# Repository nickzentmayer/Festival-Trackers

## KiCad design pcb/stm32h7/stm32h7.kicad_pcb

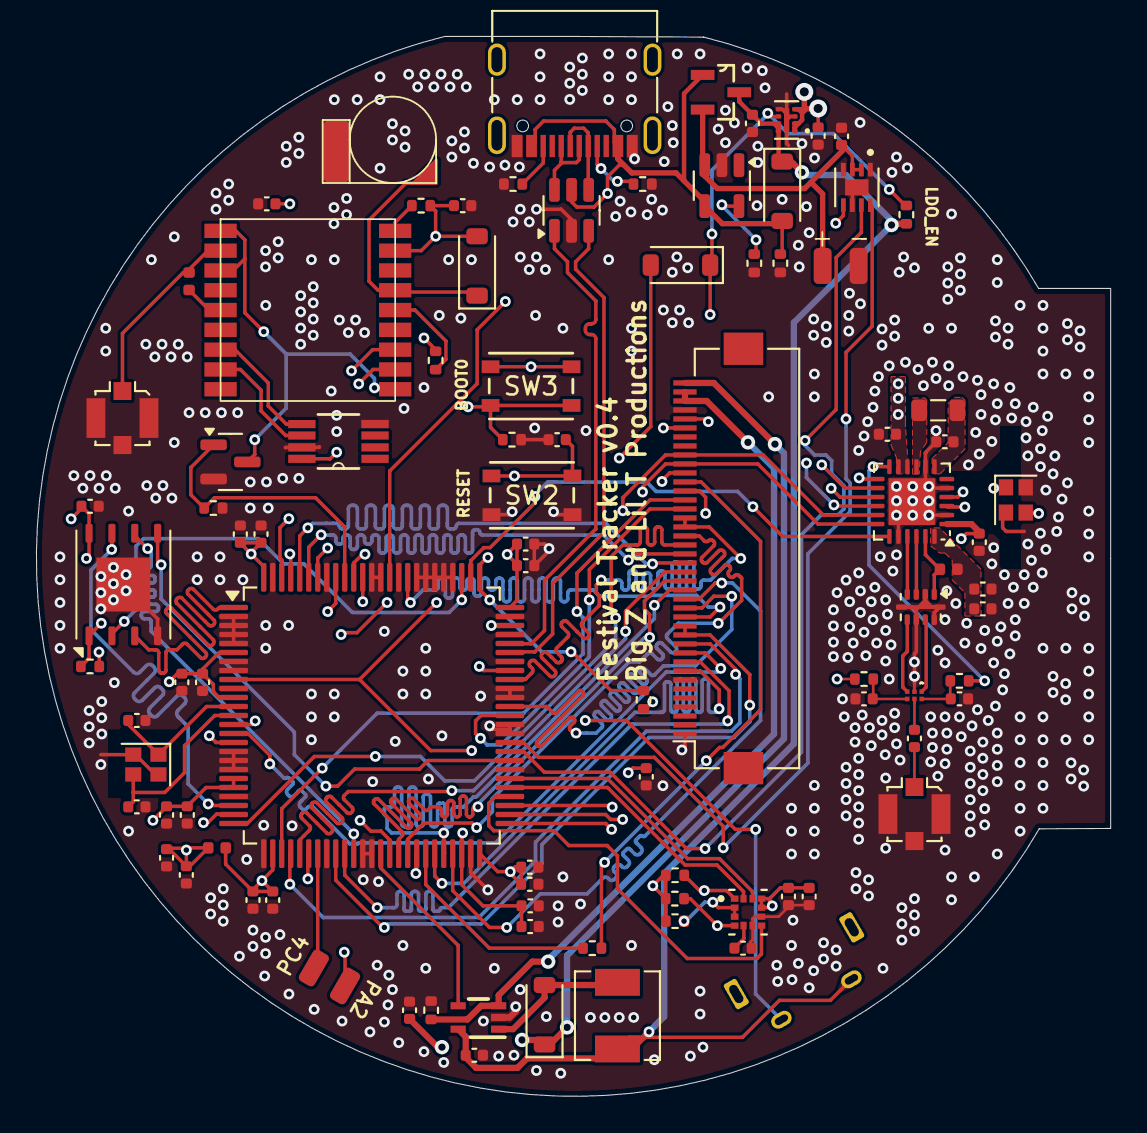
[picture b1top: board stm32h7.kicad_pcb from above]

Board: 6 copper layers, 59.7 x 58.9 mm, 93 parts (0 on the bottom side), 95 nets.

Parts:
ATGM336H1: ATGM336H
BT1: MS421R; MSR421R
C1, C2: 200nF; C_0402_1005Metric
C3, C7, C9, C12, C17, C22: 1uF; C_0402_1005Metric
C4, C5: 8pF; C_0402_1005Metric
C6, C8, C10, C11, C13, C16, C18, C24, C25, C26, C27, C28, C29, C30, C34, C35, C36, C37, C38: 100nF; C_0402_1005Metric
C14: 4.7uF; C_0402_1005Metric
C15, C39: 10uF; C_0402_1005Metric
C19: 39pF; C_0402_1005Metric
C20: 47nF; C_0402_1005Metric
C21: 470nF; C_0402_1005Metric
C23: 47pF; C_0402_1005Metric
C31, C32: 1nF; C_0402_1005Metric
C33: 220nF; C_0402_1005Metric
D1, D2, D3, D4: MBR0540; D_SOD-123
FB1: FerriteBead; L_0402_1005Metric
FL1: 0900FM15K0039; Balun_Johanson_0900FM15K0039
J1: USB_C_Receptacle_USB2.0_14P; USB_C_Receptacle_G-Switch_GT-USB-7010ASV
J2: Battery; 2 Wire Pads
J3: GPS_ANT; U.FL_Molex_MCRF_73412-0110_Vertical
J4: Conn_Coaxial; U.FL_Molex_MCRF_73412-0110_Vertical
J5: Conn_01x40_Socket; Hirose_FH12-40S-0.5SH_1x40-1MP_P0.50mm_Horizontal
J6: Test Pads; 2 Wire Pads
L1: 4.7uH; L_Sunlord_MWSA0402S
L3, L5: 47nH; L_0402_1005Metric
L4: 15uH; L_0805_2012Metric
Q1: DMG3414U; SOT-23
Q1_Xtal1: 32.0MHz; Crystal_SMD_2016-4Pin_2.0x1.6mm
R1, R4, R10, R18: 10k; R_0402_1005Metric
R2: 10R; R_0402_1005Metric
R3: 200k; R_0402_1005Metric
R5, R12, R13: 100R; R_0402_1005Metric
R6, R7, R8: 5.1k; R_0402_1005Metric
R9: 100k; R_0402_1005Metric
R11: 0R; R_0402_1005Metric
R15, R16, R17, R19: 10K; R_0402_1005Metric
SW1: SW_Push; vert_button_6mm
SW2, SW3: SW_Push; SW4_PTS815 SJM 250 SMTR LFS_CNK
U1: STM32H743VGTx; LQFP-100_14x14mm_P0.5mm
U2: NCP186AMX330TAG; PSON40P160X120X45-9N
U3: USBLC6-2SC6; SOT-23-6
U4: MCP73831-2-OT; SOT-23-5
U5: 24AA32AF-I_MS; SOP65P490X110-8N
U6: SX1262IMLTRT; QFN-24-1EP_4x4mm_P0.5mm_EP2.6x2.6mm
U7: DMG3415U-7; SOT95P240X105-3N
U8: LSM303AGR; PQFN50P200X200X100-12N
U9: MT25QUxxxxxx1xW7; W-PDFN-8-1EP_6x5mm_P1.27mm_EP3x3mm
U10: MAX17048G_T10; SON50P200X200X80-9N
U11: TPS61169DCKR; DCK0005A_N
U12: BGS12SN6E6327XTSA1; TSNP-6-2&slash_-8_INF
Y1: 25MHz; Crystal_SMD_2016-4Pin_2.0x1.6mm

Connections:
+3V3: ATGM336H1.8 (VCC), C7.1, C8.1, C9.1, C10.1, C11.1, C12.2, C15.1, C16.1, C17.1, C18.1, C24.1, C25.1, C26.1, C27.1, C28.1, C29.1, C30.1, C34.1, C35.1, C36.1, C37.1, C38.2, C39.2, D2.2 (A), FB1.1, FB1.2, J5.36, R3.1, R4.1, R13.2, R15.1, R16.1, R17.1, R18.2, R19.2, SW3.1, SW3.2, U1.6 (VBAT), U1.11 (VDD), U1.20 (VREF+), U1.21 (VDDA), U1.27 (VDD), U1.50 (VDD), U1.75 (VDD), U1.100 (VDD), U2.1 (OUT), U2.2 (OUT__1), U2.4 (FB/ADJ), U5.8 (VCC), U6.1 (VDD_IN), U6.10 (VBAT), U6.11 (VBAT_IO), U8.9 (VDD), U8.10 (VDD_IO), U9.8 (VCC)
+BATT: C13.1, J2.1, U4.3 (V_{BAT}), U7.2 (S), U10.2 (CELL), U10.3 (VDD)
/Accel & Magnetometer/CS_MAG: R15.2, U8.2 (CS_XL), U8.3 (CS_MAG)
/gps/ON/OFF: ATGM336H1.5 (ON/OFF), R4.2
ANT_SW_CTRL: R12.2, U6.12 (DIO2)
BL_ANODE: C22.2, D3.1 (K), J5.40
BL_CATHODE: J5.38, J5.39, R2.2, U11.3 (FB)
BTN: D4.2 (A), SW1.1, U1.9 (PC15)
FG_NALERT: U1.86 (PD5), U10.5 (~ALERT)
GND: BT1.2 (-), C1.1, C2.1, C3.1, C4.2, C5.1, C6.1, C7.2, C8.2, C9.2, C10.2, C11.2, C12.1, C13.2, C14.2, C15.2, C16.2, C17.2, C18.2, C20.2, C21.2, C22.1, C23.2, C24.2, C25.2, C26.2, C27.2, C28.2, C29.2, C30.2, C31.2, C32.2, C33.2, C34.2, C35.2, C36.2, C37.2, C38.1, C39.1, FL1.2 (GND), FL1.5 (GND), FL1.7 (GND), FL1.9 (GND), FL1.10 (GND), J1.A1 (GND), J1.A12 (GND), J1.B1 (GND), J1.B12 (GND), J2.2, J3.2 (Ext), J4.2 (Ext), J5.1, J5.7, J5.37, Q1.2 (S), Q1_Xtal1.2, Q1_Xtal1.4, R1.2, R2.1, R6.2, R7.2, R8.2, R9.2, R10.1, SW2.3, SW2.4, U1.2 (PE3), U1.3 (PE4), U1.4 (PE5), U1.5 (PE6), U1.7 (PC13), U1.8 (PC14), U1.10 (VSS), U1.17 (PC2_C), U1.18 (PC3_C), U1.19 (VSSA), U1.22 (PA0), U1.26 (VSS), U1.33 (PC5), U1.37 (PE7), U1.38 (PE8), U1.49 (VSS), U1.57 (PD10), U1.61 (PD14), U1.62 (PD15), U1.65 (PC8), U1.66 (PC9), U1.69 (PA10), U1.72 (PA13), U1.74 (VSS), U1.79 (PC11), U1.80 (PC12), U1.81 (PD0), U1.82 (PD1), U1.83 (PD2), U1.85 (PD4), U1.87 (PD6), U1.88 (PD7), U1.93 (PB7), U1.99 (VSS), U2.3 (N/C), U2.5 (GND), U2.9 (EPAD), U3.2 (GND), U4.2 (V_{SS}), U5.4 (VSS), U5.7 (WP), U6.2 (GND), U6.5 (GND), U6.8 (GND), U6.20 (GND), U6.25 (GND), U8.6 (GND), U8.8 (GND), U9.4 (VSS), U9.9 (PAD), U10.1 (CTG), U10.4 (GND), U10.6 (QSTRT), U10.9 (EP), U11.2 (GND), U12.2 (GND), Y1.2, Y1.4
GPS_ON: Q1.1 (G), R10.2, U1.91 (PB5)
GPS_RESET: ATGM336H1.9 (nReset), R3.2
GPS_RXD: ATGM336H1.3 (RXD), U1.98 (PE1)
GPS_TXD: ATGM336H1.2 (TXD), U1.97 (PE0)
INT_MAG: U1.54 (PB15), U8.7 (INT_MAG/DRDY)
LCD_B1: J5.24, J5.25, U1.67 (PA8)
LCD_B2: J5.23, U1.42 (PE12)
LCD_B3: J5.22, U1.25 (PA3)
LCD_B4: J5.21, U1.95 (PB8)
LCD_B5: J5.20, U1.96 (PB9)
LCD_BL: U1.39 (PE9), U11.4 (CTRL)
LCD_CS: J5.30, R19.1, U1.76 (PA14)
LCD_DE: J5.28, U1.43 (PE13)
LCD_G0: J5.19, U1.30 (PA6)
LCD_G1: J5.18, U1.41 (PE11)
LCD_G2: J5.17, U1.46 (PB10)
LCD_G3: J5.16, U1.47 (PB11)
LCD_G4: J5.15, U1.64 (PC7)
LCD_G5: J5.14, U1.84 (PD3)
LCD_HSYNC: J5.26, U1.63 (PC6)
LCD_PCLK: R5.1, U1.44 (PE14)
LCD_R1: J5.12, J5.13, U1.34 (PB0)
LCD_R2: J5.11, U1.29 (PA5)
LCD_R3: J5.10, U1.15 (PC0)
LCD_R4: J5.9, U1.35 (PB1)
LCD_R5: J5.8, U1.45 (PE15)
LCD_RST: J5.35, U1.40 (PE10)
LCD_VSYNC: J5.27, U1.28 (PA4)
LDO_EN: D4.1 (K), R11.1, U1.16 (PC1), U2.6 (EN)
LoRa_BUSY: U1.53 (PB14), U6.14 (BUSY)
LoRa_DIO1: U1.52 (PB13), U6.13 (DIO1)
LoRa_NSS: U1.77 (PA15), U6.19 (NSS)
LoRa_RST: U1.51 (PB12), U6.15 (~RESET)
MISO: U1.90 (PB4), U6.16 (MISO)
MOSI: J5.32, U1.31 (PA7), U6.17 (MOSI)
NRST: C6.2, SW2.1, SW2.2, U1.14 (NRST)
unnamed: ATGM336H1.1 (GND), Q1.3 (D)
unnamed: ATGM336H1.11 (RF_IN), J3.1 (In), L3.1
unnamed: ATGM336H1.17 (SCL), U5.6 (SCL)
unnamed: ATGM336H1.16 (SDA), U5.5 (SDA)
unnamed: ATGM336H1.6 (VBAT), BT1.1 (+), D2.1 (K)
unnamed: ATGM336H1.14 (VCC_RF), L3.2
unnamed: C1.2, C2.2, U1.48 (VCAP), U1.73 (VCAP)
unnamed: D3.2 (A), L1.2, U11.1 (SW)
unnamed: FL1.3 (RFI_N), U6.22 (RFI_N)
unnamed: FL1.4 (RFI_P), U6.21 (RFI_P)
unnamed: FL1.1 (RFO), L5.2, U6.23 (RFO)
unnamed: FL1.6 (SW_RFI), U12.3 (RF1)
unnamed: FL1.8 (SW_RFO), U12.1 (RF2)
unnamed: J1.A5 (CC1), R7.1
unnamed: J1.B5 (CC2), R6.1
unnamed: J1.A6 (D+), J1.B6 (D+), U3.6 (I/O1)
unnamed: J1.A7 (D-), J1.B7 (D-), U3.4 (I/O2)
unnamed: C19.1, J4.1 (In)
unnamed: J5.29, R5.2
unnamed: J6.1, U1.32 (PC4)
unnamed: J6.2, U1.24 (PA2)
unnamed: R1.1, SW3.3, SW3.4, U1.94 (BOOT0)
unnamed: R8.1, U4.5 (PROG)
unnamed: L4.1, U6.9 (DCC_SW)
unnamed: C21.1, L4.2, U6.7 (VREG)
unnamed: C20.1, C23.1, L5.1, U6.24 (VR_PA)
unnamed: Q1_Xtal1.3, U6.3 (XTA)
unnamed: Q1_Xtal1.1, U6.4 (XTB)
unnamed: C33.1, U8.5 (C1)
unnamed: C31.1, R12.1, U12.6 (CTRL)
unnamed: C19.2, U12.5 (RFIN)
unnamed: C32.1, R13.1, U12.4 (VDD)
PH0: C5.2, U1.12 (PH0), Y1.1
PH1: C4.1, U1.13 (PH1), Y1.3
QSPI_CLK: U1.36 (PB2), U9.6 (C)
QSPI_D0: U1.58 (PD11), U9.5 (DQ0)
QSPI_D1: U1.78 (PC10), U9.2 (DQ1)
QSPI_D2: U1.1 (PE2), U9.3 (~W/DQ2)
QSPI_D3: U1.23 (PA1), U9.7 (~RESET/DQ3)
QSPI_NCS: R18.1, U1.92 (PB6), U9.1 (~S)
SCK: J5.31, U1.89 (PB3), U6.18 (SCK)
SCL: R16.2, U1.59 (PD12), U8.1 (SCL/SPC), U10.7 (SCL)
SDA: R17.2, U1.60 (PD13), U8.4 (SDA/SDI/SDO), U10.8 (SDA)
USB_D+: U1.71 (PA12), U3.1 (I/O1)
USB_D-: U1.70 (PA11), U3.3 (I/O2)
VBUS: D1.2 (A), J1.A4 (VBUS), J1.A9 (VBUS), J1.B4 (VBUS), J1.B9 (VBUS), R9.1, U1.68 (PA9), U3.5 (VBUS), U4.4 (V_{DD}), U7.1 (G)
VCC: C3.2, C14.1, D1.1 (K), L1.1, R11.2, SW1.2, U2.7 (IN), U2.8 (IN__1), U7.3 (D), U11.5 (VIN)
XL_INT0: U1.55 (PD8), U8.12 (INT_1_XL)
XL_INT1: U1.56 (PD9), U8.11 (INT_2_XL)

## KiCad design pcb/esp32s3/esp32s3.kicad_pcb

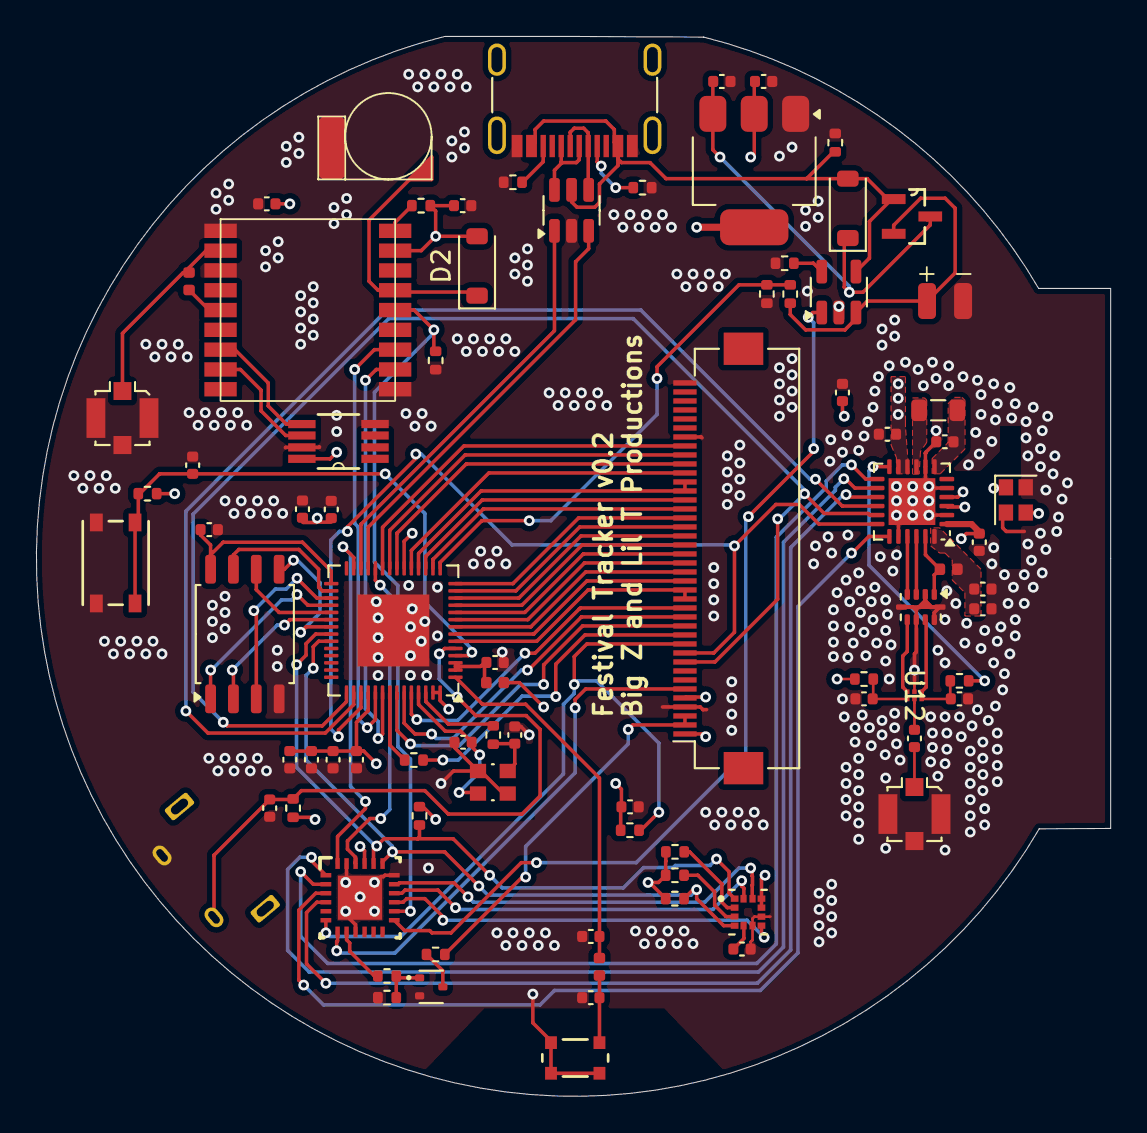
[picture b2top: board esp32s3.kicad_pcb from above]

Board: 4 copper layers, 59.7 x 58.9 mm, 83 parts (0 on the bottom side), 97 nets.

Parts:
ATGM336H1: ATGM336H
BT1: MS421R; MSR421R
C1, C5: 10pF; C_0402_1005Metric
C2: 2.4pF; C_0402_1005Metric
C3, C7, C8, C9, C10, C11, C16, C18, C22, C24, C25, C26: 100nF; C_0402_1005Metric
C4: 2.7pF; C_0402_1005Metric
C6, C12, C13, C15: 10uF; C_0402_1005Metric
C14: 22uF; C_0402_1005Metric
C17: 1uF; C_0402_1005Metric
C19: 39pF; C_0402_1005Metric
C20: 47nF; C_0402_1005Metric
C21: 470nF; C_0402_1005Metric
C23: 47pF; C_0402_1005Metric
C31, C32: 1nF; C_0402_1005Metric
C33: 220nF; C_0402_1005Metric
D1, D2: MBR0540; D_SOD-123
FL1: 0900FM15K0039; Balun_Johanson_0900FM15K0039
J1: USB_C_Receptacle_USB2.0_14P; USB_C_Receptacle_G-Switch_GT-USB-7010ASV
J2: Battery; 2 Wire Pads
J3: GPS_ANT; U.FL_Molex_MCRF_73412-0110_Vertical
J4: Conn_Coaxial; U.FL_Molex_MCRF_73412-0110_Vertical
J5: Conn_01x40_Socket; Hirose_FH12-40S-0.5SH_1x40-1MP_P0.50mm_Horizontal
L1: 2.4nH; L_0402_1005Metric
L2: 2.2nH; L_0402_1005Metric
L3, L5: 47nH; L_0402_1005Metric
L4: 15uH; L_0805_2012Metric
Q1_Xtal1: 32.0MHz; Crystal_SMD_2016-4Pin_2.0x1.6mm
Q3: DMG1012T; SOT-523
R1: 10k; R_0402_1005Metric
R2, R6, R7, R8, R24: 5.1k; R_0402_1005Metric
R3, R4, R10, R11: 200k; R_0402_1005Metric
R5: 100; R_0402_1005Metric
R9: 100k; R_0402_1005Metric
R12, R13: 100R; R_0402_1005Metric
R14, R15, R16, R17, R19, R22: 10K; R_0402_1005Metric
R18: 22; R_0402_1005Metric
R23: 10; R_0402_1005Metric
SW1: BOOT; vert_button_6mm
SW2: PTS815 SJM 250 SMTR LFS; SW4_PTS815 SJM 250 SMTR LFS_CNK
U1: ESP32-S3N8; QFN-56-1EP_7x7mm_P0.4mm_EP4x4mm
U2: AZ1117-3.3; SOT-223-3_TabPin2
U3: USBLC6-2SC6; SOT-23-6
U4: MCP73831-2-OT; SOT-23-5
U5: 24AA32AF-I_MS; SOP65P490X110-8N
U6: SX1262IMLTRT; QFN-24-1EP_4x4mm_P0.5mm_EP2.6x2.6mm
U7: DMG3415U-7; SOT95P240X105-3N
U8: LSM303AGR; PQFN50P200X200X100-12N
U9: 2450AT18D0100E; 2450AT18D0100E_JOT
U10: W25Q128JVS; SOIC-8_5.23x5.23mm_P1.27mm
U11: TCA9539RGER; RGE0024B
U12: BGS12SN6E6327XTSA1; TSNP-6-2&slash_-8_INF
X1: 40MHz; XTAL_ABM10-40.000MHZ-D30-T3

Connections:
+3V3: ATGM336H1.8 (VCC), C6.1, C7.1, C8.1, C9.1, C11.1, C12.1, C14.1, C15.1, C16.1, C17.1, C18.1, C24.1, C25.2, D2.2 (A), J5.1, J5.5, L2.2, R1.2, R2.1, R3.1, R13.2, R14.1, R15.1, R16.1, R17.1, R19.2, U1.20 (VDD3P3_RTC), U1.46 (VDD3P3_CPU), U1.55 (VDDA), U1.56 (VDDA), U2.2 (VO), U5.8 (VCC), U6.1 (VDD_IN), U6.10 (VBAT), U6.11 (VBAT_IO), U8.9 (VDD), U8.10 (VDD_IO), U11.21 (VCC)
+BATT: J2.1, R10.1, U4.3 (V_{BAT}), U7.2 (S)
/Accel & Magnetometer/CS_MAG: R15.2, U8.3 (CS_MAG)
/Accel & Magnetometer/CS_XL: R14.2, U8.2 (CS_XL)
ANT_SW_CTRL: R12.2, U6.12 (DIO2)
BAT_V: R10.2, R11.1, U1.15 (GPIO10)
CHG_STAT: U4.1 (STAT), U11.13
CHIP_PU: C26.1, R1.1, SW2.1, U1.4 (CHIP_PU)
GND: ATGM336H1.1 (GND), BT1.2 (-), C1.2, C2.2, C3.2, C4.2, C5.2, C6.2, C7.2, C8.2, C9.2, C10.2, C11.2, C12.2, C13.2, C14.2, C15.2, C16.2, C17.2, C18.2, C20.2, C21.2, C22.2, C23.2, C24.2, C25.1, C26.2, C31.2, C32.2, C33.2, FL1.2 (GND), FL1.5 (GND), FL1.7 (GND), FL1.9 (GND), FL1.10 (GND), J1.A1 (GND), J1.A12 (GND), J1.B1 (GND), J1.B12 (GND), J2.2, J3.2 (Ext), J4.2 (Ext), J5.4, J5.34, J5.40, Q1_Xtal1.2, Q1_Xtal1.4, Q3.2 (S), R4.2, R6.2, R7.2, R8.2, R9.2, R11.2, R22.1, SW1.1, SW2.2 (4), U1.57 (GND), U2.1 (GND), U3.2 (GND), U4.2 (V_{SS}), U5.4 (VSS), U5.7 (WP), U6.2 (GND), U6.5 (GND), U6.8 (GND), U6.20 (GND), U6.25 (GND), U8.6 (GND), U8.8 (GND), U9.2 (GND), U9.3 (GND), U9.4 (GND/FEED), U10.4 (GND), U11.9 (GND), U11.18 (A0), U11.23 (A1), U11.25 (EP), U12.2 (GND), X1.2 (GND), X1.4 (GND__1)
GP0: C3.1, R2.2, SW1.2, U1.5 (GPIO0)
GPIO_INT: U1.24 (GPIO18), U11.22 (INT_N)
GPIO_RST: U1.27 (GPIO21), U11.24 (RESET_N)
GPS_ON: ATGM336H1.5 (ON/OFF), R4.1, U11.14
GPS_RESET: ATGM336H1.9 (nReset), R3.2
GPS_RXD: ATGM336H1.3 (RXD), U1.47 (MTDI)
GPS_TXD: ATGM336H1.2 (TXD), U1.48 (MTMS)
INT_MAG: U8.7 (INT_MAG/DRDY), U11.15
LCD_B1: J5.16, J5.17, U1.6 (GPIO1)
LCD_B2: J5.18, U1.7 (GPIO2)
LCD_B3: J5.19, U1.8 (GPIO3)
LCD_B4: J5.20, U1.9 (GPIO4)
LCD_B5: J5.21, U1.10 (GPIO5)
LCD_BL: R24.1, U11.8 (P07)
LCD_CS: J5.11, R19.1, U11.6 (P05)
LCD_DE: J5.13, U1.50 (U0RXD)
LCD_G0: J5.22, U1.11 (GPIO6)
LCD_G1: J5.23, U1.12 (GPIO7)
LCD_G2: J5.24, U1.13 (GPIO8)
LCD_G3: J5.25, U1.14 (GPIO9)
LCD_G4: J5.26, U1.16 (GPIO11)
LCD_G5: J5.27, U1.17 (GPIO12)
LCD_HSYNC: J5.15, U1.52 (GPIO46)
LCD_PCLK: R5.1, U1.49 (U0TXD)
LCD_R1: J5.28, J5.29, U1.18 (GPIO13)
LCD_R2: J5.30, U1.19 (GPIO14)
LCD_R3: J5.31, U1.21 (XTAL_32K_P)
LCD_R4: J5.32, U1.22 (XTAL_32K_N)
LCD_R5: J5.33, U1.23 (GPIO17)
LCD_RST: J5.6, U11.7 (P06)
LCD_VSYNC: J5.14, U1.51 (GPIO45)
LNA_IN: C4.1, L1.1, U1.1 (LNA_IN)
LoRa_BUSY: U6.14 (BUSY), U11.1 (P00)
LoRa_DIO1: U6.13 (DIO1), U11.2 (P01)
LoRa_NSS: U6.19 (NSS), U11.3 (P02)
LoRa_RST: U6.15 (~RESET), U11.4 (P03)
MISO: U1.44 (MTCK), U6.16 (MISO)
MOSI: J5.9, U1.43 (GPIO38), U6.17 (MOSI)
unnamed: ATGM336H1.11 (RF_IN), J3.1 (In), L3.1
unnamed: ATGM336H1.17 (SCL), U5.6 (SCL)
unnamed: ATGM336H1.16 (SDA), U5.5 (SDA)
unnamed: ATGM336H1.6 (VBAT), BT1.1 (+), D2.1 (K)
unnamed: ATGM336H1.14 (VCC_RF), L3.2
unnamed: C1.1, R18.2, X1.1
unnamed: C10.1, L2.1, U1.2 (VDD3P3), U1.3 (VDD3P3)
unnamed: FL1.3 (RFI_N), U6.22 (RFI_N)
unnamed: FL1.4 (RFI_P), U6.21 (RFI_P)
unnamed: FL1.1 (RFO), L5.2, U6.23 (RFO)
unnamed: FL1.6 (SW_RFI), U12.3 (RF1)
unnamed: FL1.8 (SW_RFO), U12.1 (RF2)
unnamed: J1.A5 (CC1), R7.1
unnamed: J1.B5 (CC2), R6.1
unnamed: J1.A6 (D+), J1.B6 (D+), U3.6 (I/O1)
unnamed: J1.A7 (D-), J1.B7 (D-), U3.4 (I/O2)
unnamed: C19.1, J4.1 (In)
unnamed: J5.2, J5.3, R23.1
unnamed: J5.12, R5.2
unnamed: Q3.3 (D), R23.2
unnamed: Q3.1 (G), R22.2, R24.2
unnamed: R8.1, U4.5 (PROG)
unnamed: L4.1, U6.9 (DCC_SW)
unnamed: C21.1, L4.2, U6.7 (VREG)
unnamed: C20.1, C23.1, L5.1, U6.24 (VR_PA)
unnamed: Q1_Xtal1.3, U6.3 (XTA)
unnamed: Q1_Xtal1.1, U6.4 (XTB)
unnamed: C33.1, U8.5 (C1)
unnamed: C2.1, L1.2, U9.1 (FEED/GND)
unnamed: C31.1, R12.1, U12.6 (CTRL)
unnamed: C19.2, U12.5 (RFIN)
unnamed: C32.1, R13.1, U12.4 (VDD)
SCK: J5.10, U1.45 (MTDO), U6.18 (SCK)
SCL: R17.2, U1.37 (SPICLK_P), U8.4 (SDA/SDI/SDO), U11.19 (SCL)
SDA: R16.2, U1.36 (SPICLK_N), U8.1 (SCL/SPC), U11.20 (SDA)
SPI_CLK: U1.33 (SPICLK), U10.6 (CLK)
SPI_CS0: U1.32 (SPICS0), U10.1 (~CS)
SPI_IO0: U1.35 (SPID), U10.5 (DI(IO0))
SPI_IO1: U1.34 (SPIQ), U10.2 (DO(IO1))
SPI_IO2: U1.31 (SPIWP), U10.3 (IO2)
SPI_IO3: U1.30 (SPIHD), U10.7 (IO3)
USB_D+: U1.26 (GPIO20/USB_D+), U3.1 (I/O1)
USB_D-: U1.25 (GPIO19/USB_D-), U3.3 (I/O2)
VBUS: D1.2 (A), J1.A4 (VBUS), J1.A9 (VBUS), J1.B4 (VBUS), J1.B9 (VBUS), R9.1, U3.5 (VBUS), U4.4 (V_{DD}), U7.1 (G)
VCC: C13.1, D1.1 (K), U2.3 (VI), U7.3 (D)
VDD_SPI: C22.1, U1.29 (VDD_SPI), U10.8 (VCC)
XL_INT0: U8.12 (INT_1_XL), U11.16
XL_INT1: U8.11 (INT_2_XL), U11.17
XTAL_N: C5.1, U1.53 (XTAL_N), X1.3
XTAL_P: R18.1, U1.54 (XTAL_P)

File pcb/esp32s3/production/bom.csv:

Designator,Footprint,Quantity,Value,LCSC Part #
ATGM336H1,ATGM336H,1,~,
BT1,MSR421R,1,MS421R,
"C1, C5",0402,2,10pF,
"C10, C11, C16, C18, C22, C24, C25, C3, C7, C8, C9",0402,11,100nF,
"C12, C13, C15, C6",0402,4,10uF,
C14,0402,1,22uF,
C17,0402,1,1uF,
C19,0402,1,39pF,
C2,0402,1,2.4pF,
C20,0402,1,47nF,
C21,0402,1,470nF,
C23,0402,1,47pF,
"C31, C32",0402,2,1nF,
C33,0402,1,220nF,
C4,0402,1,2.7pF,
"D1, D2",D_SOD-123,2,MBR0540,
FL1,Balun_Johanson_0900FM15K0039,1,0900FM15K0039,
J1,USB_C_Receptacle_G-Switch_GT-USB-7010ASV,1,USB_C_Receptacle_USB2.0_14P,
J2,2 Wire Pads,1,Battery,
J3,U.FL_Molex_MCRF_73412-0110_Vertical,1,GPS_ANT,
J4,U.FL_Molex_MCRF_73412-0110_Vertical,1,Conn_Coaxial,
J5,Hirose_FH12-40S-0.5SH_1x40-1MP_P0.50mm_Horizontal,1,Conn_01x40_Socket,
L1,0402,1,2.4nH,
L2,0402,1,2.2nH,
"L3, L5",0402,2,47nH,
L4,0805,1,15uH,
Q1_Xtal1,Crystal_SMD_2016-4Pin_2.0x1.6mm,1,32.0MHz,
Q3,SOT-523,1,DMG1012T,
"R1, R14, R15, R16, R17, R19, R22",0402,7,10k,
"R10, R11, R3, R4",0402,4,200k,
"R12, R13",0402,2,100R,
R18,0402,1,22,
"R2, R24, R6, R7, R8",0402,5,5.1k,
R23,0402,1,10,
R5,0402,1,100,
R9,0402,1,100k,
SW1,vert_button_6mm,1,BOOT,
SW2,SW4_PTS815 SJM 250 SMTR LFS_CNK,1,PTS815 SJM 250 SMTR LFS,
U1,QFN-56-1EP_7x7mm_P0.4mm_EP4x4mm,1,ESP32-S3N8,
U10,SOIC-8_5.23x5.23mm_P1.27mm,1,W25Q128JVS,
U11,RGE0024B,1,TCA9539RGER,
U12,TSNP-6-2&slash_-8_INF,1,BGS12SN6E6327XTSA1,
U2,SOT-223-3_TabPin2,1,AZ1117-3.3,
U3,SOT-23-6,1,USBLC6-2SC6,
U4,SOT-23-5,1,MCP73831-2-OT,
U5,SOP65P490X110-8N,1,24AA32AF-I_MS,24AA32AF-I/MS
U6,QFN-24-1EP_4x4mm_P0.5mm_EP2.6x2.6mm,1,SX1262IMLTRT,
U7,SOT95P240X105-3N,1,DMG3415U-7,DMG3415U-7
U8,PQFN50P200X200X100-12N,1,LSM303AGR,
U9,2450AT18D0100E_JOT,1,2450AT18D0100E,
X1,Crystal_SMD_Abracon_ABM10-4Pin_2.5x2.0mm,1,40MHz,

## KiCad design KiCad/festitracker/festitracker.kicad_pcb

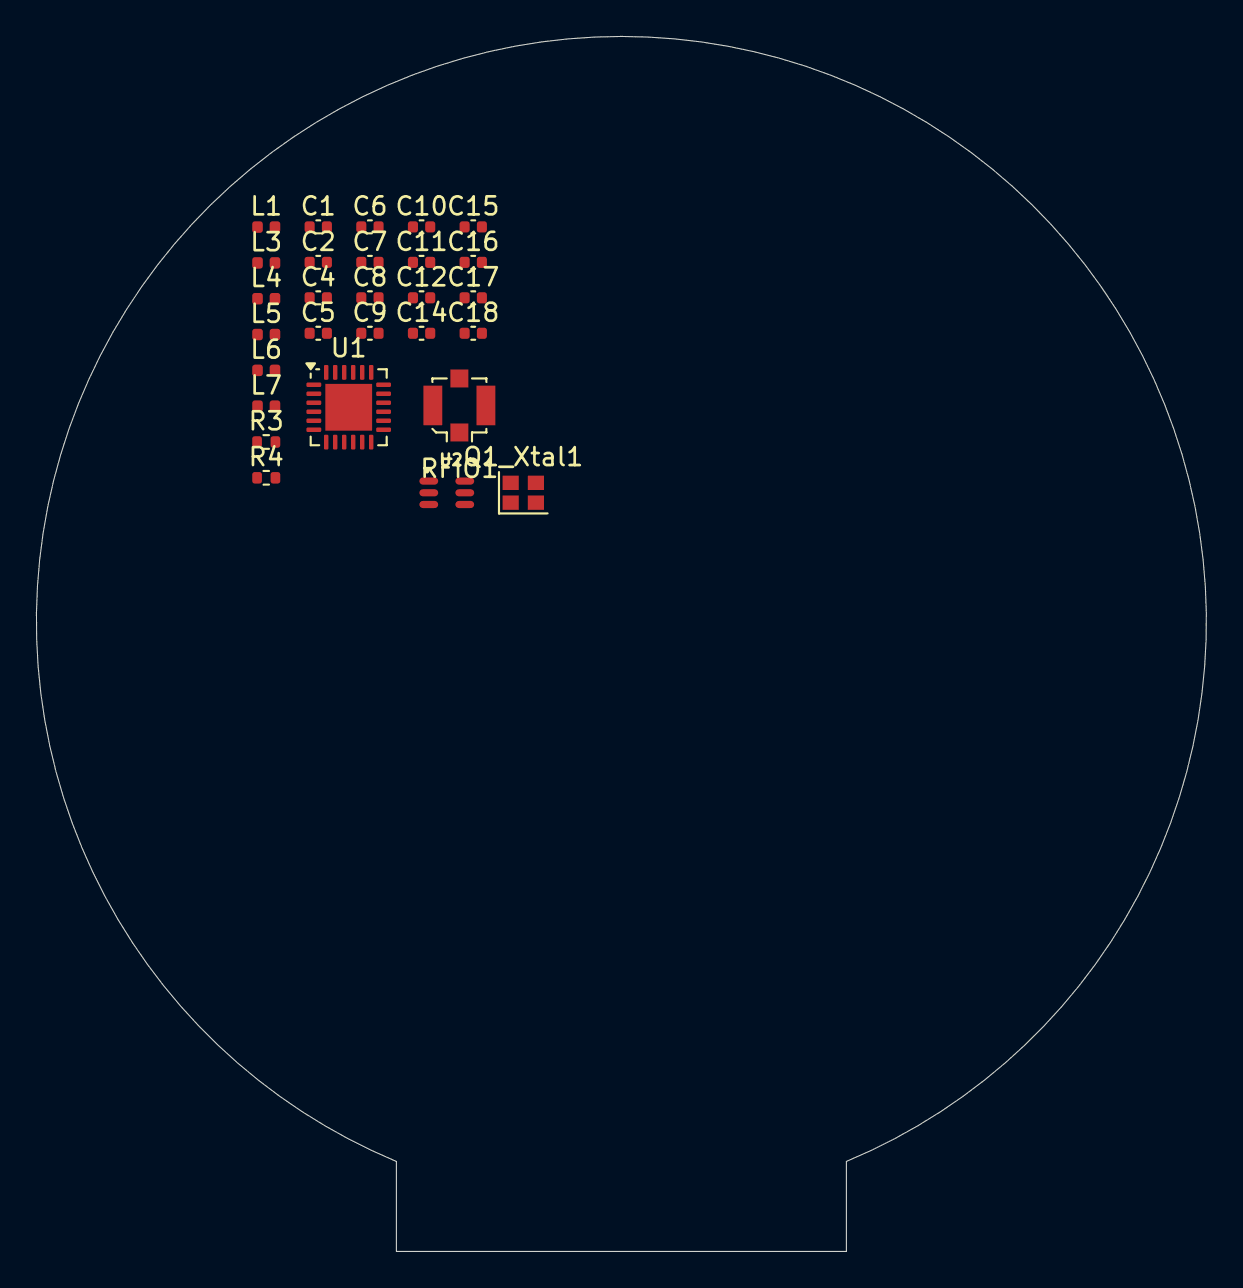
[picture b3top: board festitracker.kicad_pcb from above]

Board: 4 copper layers, 65.0 x 67.5 mm, 28 parts (0 on the bottom side), 20 nets, no tracks yet.

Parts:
C1: 47nF; C_0402_1005Metric
C2: 47pF; C_0402_1005Metric
C4: 3pF; C_0402_1005Metric
C5: 5.6pF; C_0402_1005Metric
C6, C8: 39pF; C_0402_1005Metric
C7, C12: 1.8pF; C_0402_1005Metric
C9, C10: 3.3pF; C_0402_1005Metric
C11: 2.4pF; C_0402_1005Metric
C14, C15: 1nF; C_0402_1005Metric
C16: 1uF; C_0402_1005Metric
C17: 470nF; C_0402_1005Metric
C18: 100nF; C_0402_1005Metric
L1: 47nH; L_0402_1005Metric
L3: 2.5nH; L_0402_1005Metric
L4: 4.7nH; L_0402_1005Metric
L5: 9.1nH; L_0402_1005Metric
L6: 15nH; L_0402_1005Metric
L7: 15uH; L_0402_1005Metric
Q1_Xtal1: 32.0MHz; Crystal_SMD_2016-4Pin_2.0x1.6mm
R3, R4: 100R; R_0402_1005Metric
RFIO1: SMA; U.FL_Molex_MCRF_73412-0110_Vertical
U1: SX1262IMLTRT; QFN-24-1EP_4x4mm_P0.5mm_EP2.6x2.6mm
U2: PE4259; SOT65P215X110-6N

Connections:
ANT_SW_CTRL: R3.2, U1.12 (DIO2)
GND: C1.2, C2.2, C5.2, C7.2, C9.2, C10.2, C12.2, C14.2, C15.2, C16.2, C17.2, C18.2, Q1_Xtal1.2, Q1_Xtal1.4, RFIO1.2 (Ext), U1.2 (GND), U1.5 (GND), U1.8 (GND), U1.20 (GND), U1.21 (RFI_P), U1.25 (GND), U2.2 (GND)
unnamed: C4.2, C5.1, C6.1, L3.2
unnamed: C6.2, L4.1
unnamed: C8.1, C9.1, L5.2
unnamed: C11.1, C12.1, L6.2
unnamed: C10.1, L5.1, RFIO1.1 (In)
unnamed: L7.1, U1.9 (DCC_SW)
unnamed: L6.1, U1.22 (RFI_N)
unnamed: C4.1, L1.2, L3.1, U1.23 (RFO)
unnamed: C17.1, L1.1, L7.2, U1.7 (VREG)
unnamed: Q1_Xtal1.3, U1.3 (XTA)
unnamed: Q1_Xtal1.1, U1.4 (XTB)
unnamed: C15.1, R3.1, U2.4 (CTRL)
unnamed: C7.1, L4.2, U2.1 (RF1)
unnamed: C11.2, U2.3 (RF2)
unnamed: C8.2, U2.5 (RFC)
unnamed: C14.1, R4.1, U2.6 (~CTRL/~VDD)
VDD_RADIO: C16.1, C18.1, U1.1 (VDD_IN), U1.10 (VBAT), U1.11 (VBAT_IO)
VR_PA: C1.1, C2.1, U1.24 (VR_PA)

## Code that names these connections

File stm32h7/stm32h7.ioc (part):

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Mcu.Name=STM32H743VGTx
Mcu.Package=LQFP100
Mcu.UserName=STM32H743VGTx
PA1.Signal=QUADSPI_BK1_IO3
PA11.Mode=Device_Only
PA11.Signal=USB_OTG_FS_DM
PA12.Mode=Device_Only
PA12.Signal=USB_OTG_FS_DP
PA14\ (JTCK/SWCLK).GPIOParameters=PinState,GPIO_PuPd,GPIO_Label
PA14\ (JTCK/SWCLK).GPIO_Label=LCD_CS
PA14\ (JTCK/SWCLK).GPIO_PuPd=GPIO_PULLUP
PA14\ (JTCK/SWCLK).PinState=GPIO_PIN_SET
PA14\ (JTCK/SWCLK).Signal=GPIO_Output
PA15\ (JTDI).GPIOParameters=GPIO_Label
PA15\ (JTDI).GPIO_Label=LORA_NSS
PA15\ (JTDI).Signal=GPIO_Output
PA2.GPIOParameters=GPIO_Label
PA2.GPIO_Label=TP_PA2
PA2.Signal=GPIO_Output
PA3.GPIOParameters=GPIO_Speed
PA3.GPIO_Speed=GPIO_SPEED_FREQ_VERY_HIGH
PA3.Mode=RGB565
PA3.Signal=LTDC_B5
PA4.GPIOParameters=GPIO_Speed
PA4.GPIO_Speed=GPIO_SPEED_FREQ_VERY_HIGH
PA4.Mode=RGB565
PA4.Signal=LTDC_VSYNC
PA5.GPIOParameters=GPIO_Speed
PA5.GPIO_Speed=GPIO_SPEED_FREQ_VERY_HIGH
PA5.Mode=RGB565
PA5.Signal=LTDC_R4
PA6.GPIOParameters=GPIO_Speed
PA6.GPIO_Speed=GPIO_SPEED_FREQ_VERY_HIGH
PA6.Mode=RGB565
PA6.Signal=LTDC_G2
PA7.GPIOParameters=GPIO_Speed,GPIO_Label
PA7.GPIO_Label=MOSI
PA7.GPIO_Speed=GPIO_SPEED_FREQ_VERY_HIGH
PA7.Signal=GPIO_Output
PA8.GPIOParameters=GPIO_Speed
PA8.GPIO_Speed=GPIO_SPEED_FREQ_VERY_HIGH
PA8.Mode=RGB565
PA8.Signal=LTDC_B3
PA9.Mode=Activate_VBUS
PA9.Signal=USB_OTG_FS_VBUS
PB0.GPIOParameters=GPIO_Speed
PB0.GPIO_Speed=GPIO_SPEED_FREQ_VERY_HIGH
PB0.Mode=RGB565
PB0.Signal=LTDC_R3
PB1.GPIOParameters=GPIO_Speed
PB1.GPIO_Speed=GPIO_SPEED_FREQ_VERY_HIGH
PB1.Mode=RGB565
PB1.Signal=LTDC_R6
PB10.GPIOParameters=GPIO_Speed
PB10.GPIO_Speed=GPIO_SPEED_FREQ_VERY_HIGH
PB10.Mode=RGB565
PB10.Signal=LTDC_G4
PB11.GPIOParameters=GPIO_Speed
PB11.GPIO_Speed=GPIO_SPEED_FREQ_VERY_HIGH
PB11.Mode=RGB565
PB11.Signal=LTDC_G5
PB12.GPIOParameters=GPIO_Label
PB12.GPIO_Label=LORA_RST
PB12.Signal=GPIO_Output
PB13.GPIOParameters=GPIO_Label
PB13.GPIO_Label=LORA_DIO1
PB13.Signal=GPIO_Input
PB14.GPIOParameters=GPIO_Label
PB14.GPIO_Label=LORA_BUSY
PB14.Signal=GPIO_Input
PB2.Signal=QUADSPI_CLK
PB3\ (JTDO/TRACESWO).GPIOParameters=GPIO_Speed,GPIO_Label
PB3\ (JTDO/TRACESWO).GPIO_Label=SCK
PB3\ (JTDO/TRACESWO).GPIO_Speed=GPIO_SPEED_FREQ_VERY_HIGH
PB3\ (JTDO/TRACESWO).Signal=GPIO_Output
PB4\ (NJTRST).GPIOParameters=GPIO_Label
PB4\ (NJTRST).GPIO_Label=MISO
PB4\ (NJTRST).Signal=GPIO_Input
PB5.GPIOParameters=GPIO_Label
PB5.GPIO_Label=GPS_ON
PB5.Signal=GPIO_Output
PB8.GPIOParameters=GPIO_Speed
PB8.GPIO_Speed=GPIO_SPEED_FREQ_VERY_HIGH
PB8.Mode=RGB565
PB8.Signal=LTDC_B6
PB9.GPIOParameters=GPIO_Speed
PB9.GPIO_Speed=GPIO_SPEED_FREQ_VERY_HIGH
PB9.Mode=RGB565
PB9.Signal=LTDC_B7
PC0.GPIOParameters=GPIO_Speed
PC0.GPIO_Speed=GPIO_SPEED_FREQ_VERY_HIGH
PC0.Mode=RGB565
PC0.Signal=LTDC_R5
PC1.GPIOParameters=GPIO_Label
PC1.GPIO_Label=LDO_EN
PC1.Signal=GPIO_Output
PC10.Signal=QUADSPI_BK1_IO1
PC15-OSC32_OUT\ (OSC32_OUT).GPIOParameters=GPIO_PuPd,GPIO_Label
PC15-OSC32_OUT\ (OSC32_OUT).GPIO_Label=BTN
PC15-OSC32_OUT\ (OSC32_OUT).GPIO_PuPd=GPIO_PULLDOWN
PC15-OSC32_OUT\ (OSC32_OUT).Signal=GPXTI15
PC4.GPIOParameters=GPIO_Label
PC4.GPIO_Label=TP_PC4
PC4.Signal=GPIO_Output
PC6.GPIOParameters=GPIO_Speed
PC6.GPIO_Speed=GPIO_SPEED_FREQ_VERY_HIGH
PC6.Mode=RGB565
PC6.Signal=LTDC_HSYNC
PC7.GPIOParameters=GPIO_Speed
PC7.GPIO_Speed=GPIO_SPEED_FREQ_VERY_HIGH
PC7.Mode=RGB565
PC7.Signal=LTDC_G6
PD11.Signal=QUADSPI_BK1_IO0
PD12.GPIOParameters=GPIO_Speed,GPIO_Pu
PD12.GPIO_Pu=GPIO_PULLUP
PD12.GPIO_Speed=GPIO_SPEED_FREQ_VERY_HIGH
PD12.Mode=I2C
PD12.Signal=I2C4_SCL
PD13.GPIOParameters=GPIO_Speed,GPIO_Pu
PD13.GPIO_Pu=GPIO_PULLUP
PD13.GPIO_Speed=GPIO_SPEED_FREQ_VERY_HIGH
PD13.Mode=I2C
PD13.Signal=I2C4_SDA
PD3.GPIOParameters=GPIO_Speed
PD3.GPIO_Speed=GPIO_SPEED_FREQ_VERY_HIGH
PD3.Mode=RGB565
PD3.Signal=LTDC_G7
PD4.GPIOParameters=GPIO_Label
PD4.GPIO_Label=BATT_STAT
PD4.Signal=GPIO_Input
PD8.GPIOParameters=GPIO_Label
PD8.GPIO_Label=XL_INT0
PD8.Signal=GPXTI8
PD9.GPIOParameters=GPIO_Label
PD9.GPIO_Label=XL_INT1
PD9.Signal=GPXTI9
PE0.Mode=Asynchronous
PE0.Signal=UART8_RX
PE1.Mode=Asynchronous
PE1.Signal=UART8_TX
PE10.GPIOParameters=PinState,GPIO_PuPd,GPIO_Label
PE10.GPIO_Label=LCD_RST
PE10.GPIO_PuPd=GPIO_NOPULL
PE10.PinState=GPIO_PIN_SET
PE10.Signal=GPIO_Output
PE11.GPIOParameters=GPIO_Speed
PE11.GPIO_Speed=GPIO_SPEED_FREQ_VERY_HIGH
PE11.Mode=RGB565
PE11.Signal=LTDC_G3
PE12.GPIOParameters=GPIO_Speed
PE12.GPIO_Speed=GPIO_SPEED_FREQ_VERY_HIGH
PE12.Mode=RGB565
PE12.Signal=LTDC_B4
PE13.GPIOParameters=GPIO_Speed
PE13.GPIO_Speed=GPIO_SPEED_FREQ_VERY_HIGH
PE13.Mode=RGB565
PE13.Signal=LTDC_DE
PE14.GPIOParameters=GPIO_Speed
PE14.GPIO_Speed=GPIO_SPEED_FREQ_VERY_HIGH
PE14.Mode=RGB565
PE14.Signal=LTDC_CLK
PE15.GPIOParameters=GPIO_Speed
PE15.GPIO_Speed=GPIO_SPEED_FREQ_VERY_HIGH
PE15.Mode=RGB565
PE15.Signal=LTDC_R7
PE9.GPIOParameters=GPIO_Label
PE9.GPIO_Label=LCD_BL
PE9.Signal=S_TIM1_CH1
PH0-OSC_IN\ (PH0).Mode=HSE-External-Oscillator
PH0-OSC_IN\ (PH0).Signal=RCC_OSC_IN
PH1-OSC_OUT\ (PH1).Mode=HSE-External-Oscillator
PH1-OSC_OUT\ (PH1).Signal=RCC_OSC_OUT
RCC.SYSCLKFreq_VALUE=475000000
RCC.SYSCLKSource=RCC_SYSCLKSOURCE_PLLCLK
board=custom

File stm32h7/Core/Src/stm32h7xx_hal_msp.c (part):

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
    __HAL_RCC_GPIOD_CLK_ENABLE();
    /**I2C4 GPIO Configuration
    PD12     ------> I2C4_SCL
    PD13     ------> I2C4_SDA
    */
    GPIO_InitStruct.Pin = GPIO_PIN_12|GPIO_PIN_13;
    GPIO_InitStruct.Mode = GPIO_MODE_AF_OD;
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    __HAL_RCC_I2C4_CLK_DISABLE();

    /**I2C4 GPIO Configuration
    PD12     ------> I2C4_SCL
    PD13     ------> I2C4_SDA
    */
    HAL_GPIO_DeInit(GPIOD, GPIO_PIN_12);

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    __HAL_RCC_GPIOE_CLK_ENABLE();
    __HAL_RCC_GPIOD_CLK_ENABLE();
    /**LTDC GPIO Configuration
    PC0     ------> LTDC_R5
    PA3     ------> LTDC_B5
    PA4     ------> LTDC_VSYNC
    PA5     ------> LTDC_R4
    PA6     ------> LTDC_G2
    PB0     ------> LTDC_R3
    PB1     ------> LTDC_R6
    PE11     ------> LTDC_G3
    PE12     ------> LTDC_B4
    PE13     ------> LTDC_DE
    PE14     ------> LTDC_CLK
    PE15     ------> LTDC_R7
    PB10     ------> LTDC_G4
    PB11     ------> LTDC_G5
    PC6     ------> LTDC_HSYNC
    PC7     ------> LTDC_G6
    PA8     ------> LTDC_B3
    PD3     ------> LTDC_G7
    PB8     ------> LTDC_B6
    PB9     ------> LTDC_B7
    */
    GPIO_InitStruct.Pin = GPIO_PIN_0|GPIO_PIN_6|GPIO_PIN_7;
    GPIO_InitStruct.Mode = GPIO_MODE_AF_PP;
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    __HAL_RCC_LTDC_CLK_DISABLE();

    /**LTDC GPIO Configuration
    PC0     ------> LTDC_R5
    PA3     ------> LTDC_B5
    PA4     ------> LTDC_VSYNC
    PA5     ------> LTDC_R4
    PA6     ------> LTDC_G2
    PB0     ------> LTDC_R3
    PB1     ------> LTDC_R6
    PE11     ------> LTDC_G3
    PE12     ------> LTDC_B4
    PE13     ------> LTDC_DE
    PE14     ------> LTDC_CLK
    PE15     ------> LTDC_R7
    PB10     ------> LTDC_G4
    PB11     ------> LTDC_G5
    PC6     ------> LTDC_HSYNC
    PC7     ------> LTDC_G6
    PA8     ------> LTDC_B3
    PD3     ------> LTDC_G7
    PB8     ------> LTDC_B6
    PB9     ------> LTDC_B7
    */
    HAL_GPIO_DeInit(GPIOC, GPIO_PIN_0|GPIO_PIN_6|GPIO_PIN_7);

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    __HAL_RCC_GPIOD_CLK_ENABLE();
    __HAL_RCC_GPIOC_CLK_ENABLE();
    /**QUADSPI GPIO Configuration
    PE2     ------> QUADSPI_BK1_IO2
    PA1     ------> QUADSPI_BK1_IO3
    PB2     ------> QUADSPI_CLK
    PD11     ------> QUADSPI_BK1_IO0
    PC10     ------> QUADSPI_BK1_IO1
    PB6     ------> QUADSPI_BK1_NCS
    */
    GPIO_InitStruct.Pin = GPIO_PIN_2;
    GPIO_InitStruct.Mode = GPIO_MODE_AF_PP;
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    __HAL_RCC_QSPI_CLK_DISABLE();

    /**QUADSPI GPIO Configuration
    PE2     ------> QUADSPI_BK1_IO2
    PA1     ------> QUADSPI_BK1_IO3
    PB2     ------> QUADSPI_CLK
    PD11     ------> QUADSPI_BK1_IO0
    PC10     ------> QUADSPI_BK1_IO1
    PB6     ------> QUADSPI_BK1_NCS
    */
    HAL_GPIO_DeInit(GPIOE, GPIO_PIN_2);

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
    __HAL_RCC_GPIOE_CLK_ENABLE();
    /**TIM1 GPIO Configuration
    PE9     ------> TIM1_CH1
    */
    GPIO_InitStruct.Pin = LCD_BL_Pin;
    GPIO_InitStruct.Mode = GPIO_MODE_AF_PP;
    GPIO_InitStruct.Pull = GPIO_NOPULL;
    GPIO_InitStruct.Speed = GPIO_SPEED_FREQ_LOW;
    GPIO_InitStruct.Alternate = GPIO_AF1_TIM1;
    HAL_GPIO_Init(LCD_BL_GPIO_Port, &GPIO_InitStruct);

  /* USER CODE BEGIN TIM1_MspPostInit 1 */

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
    __HAL_RCC_GPIOE_CLK_ENABLE();
    /**UART8 GPIO Configuration
    PE0     ------> UART8_RX
    PE1     ------> UART8_TX
    */
    GPIO_InitStruct.Pin = GPIO_PIN_0|GPIO_PIN_1;
    GPIO_InitStruct.Mode = GPIO_MODE_AF_PP;
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    __HAL_RCC_UART8_CLK_DISABLE();

    /**UART8 GPIO Configuration
    PE0     ------> UART8_RX
    PE1     ------> UART8_TX
    */
    HAL_GPIO_DeInit(GPIOE, GPIO_PIN_0|GPIO_PIN_1);

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
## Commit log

2024-03-25 board config for platformio
2024-03-25 Remove unnecessary entries from .gitignore
2024-03-25 tft working
2024-04-12 tilt test
2024-04-19 whole lotta stuff
2024-04-19 updated kicad proj
2024-04-19 kicad_pcb
2024-04-21 updated footprints / schematic
2024-04-22 pcb update!!!
2024-05-28 Update PCB with new components and footprints
2024-05-30 pcb kinda almost done!
2024-05-30 LORA
2024-05-31 finishing touches
2024-06-14 fix power circuit
2024-06-14 changed so exact same mosfet placement
2024-07-19 moved display connector to correct position
2024-08-09 added "stm32h7" new pcb and docs
2024-08-12 routing done
2024-08-12 fixed some footprints and added power switching mosfet for gps
2024-08-13 is it finally done or am i going insane
2024-08-13 using EN on the LDO for power switch now
2024-08-14 fixed some wiring
2024-08-15 idek what i did
2024-08-19 finished pcb, ordered v0.3
2024-09-23 ugh.... 6 layer....
2024-09-23 everything is connected....
2024-09-23 finishing touches, sent to jlcpcb
2024-10-18 Update st7701.c and st7701.h files
2024-10-19 power latch working, lcd backlight working
2024-10-20 tried bit-banging 9 bit spi
2024-10-22 display working
2024-10-22 dma2d black fill, basic graphics draw good

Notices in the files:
stm32h7/Core/Src/stm32h7xx_hal_msp.c:
Copyright (c) 2024 STMicroelectronics.
All rights reserved.
This software is licensed under terms that can be found in the LICENSE file
